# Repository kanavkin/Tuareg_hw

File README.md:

# Tuareg_hw
Tuareg board and schematics

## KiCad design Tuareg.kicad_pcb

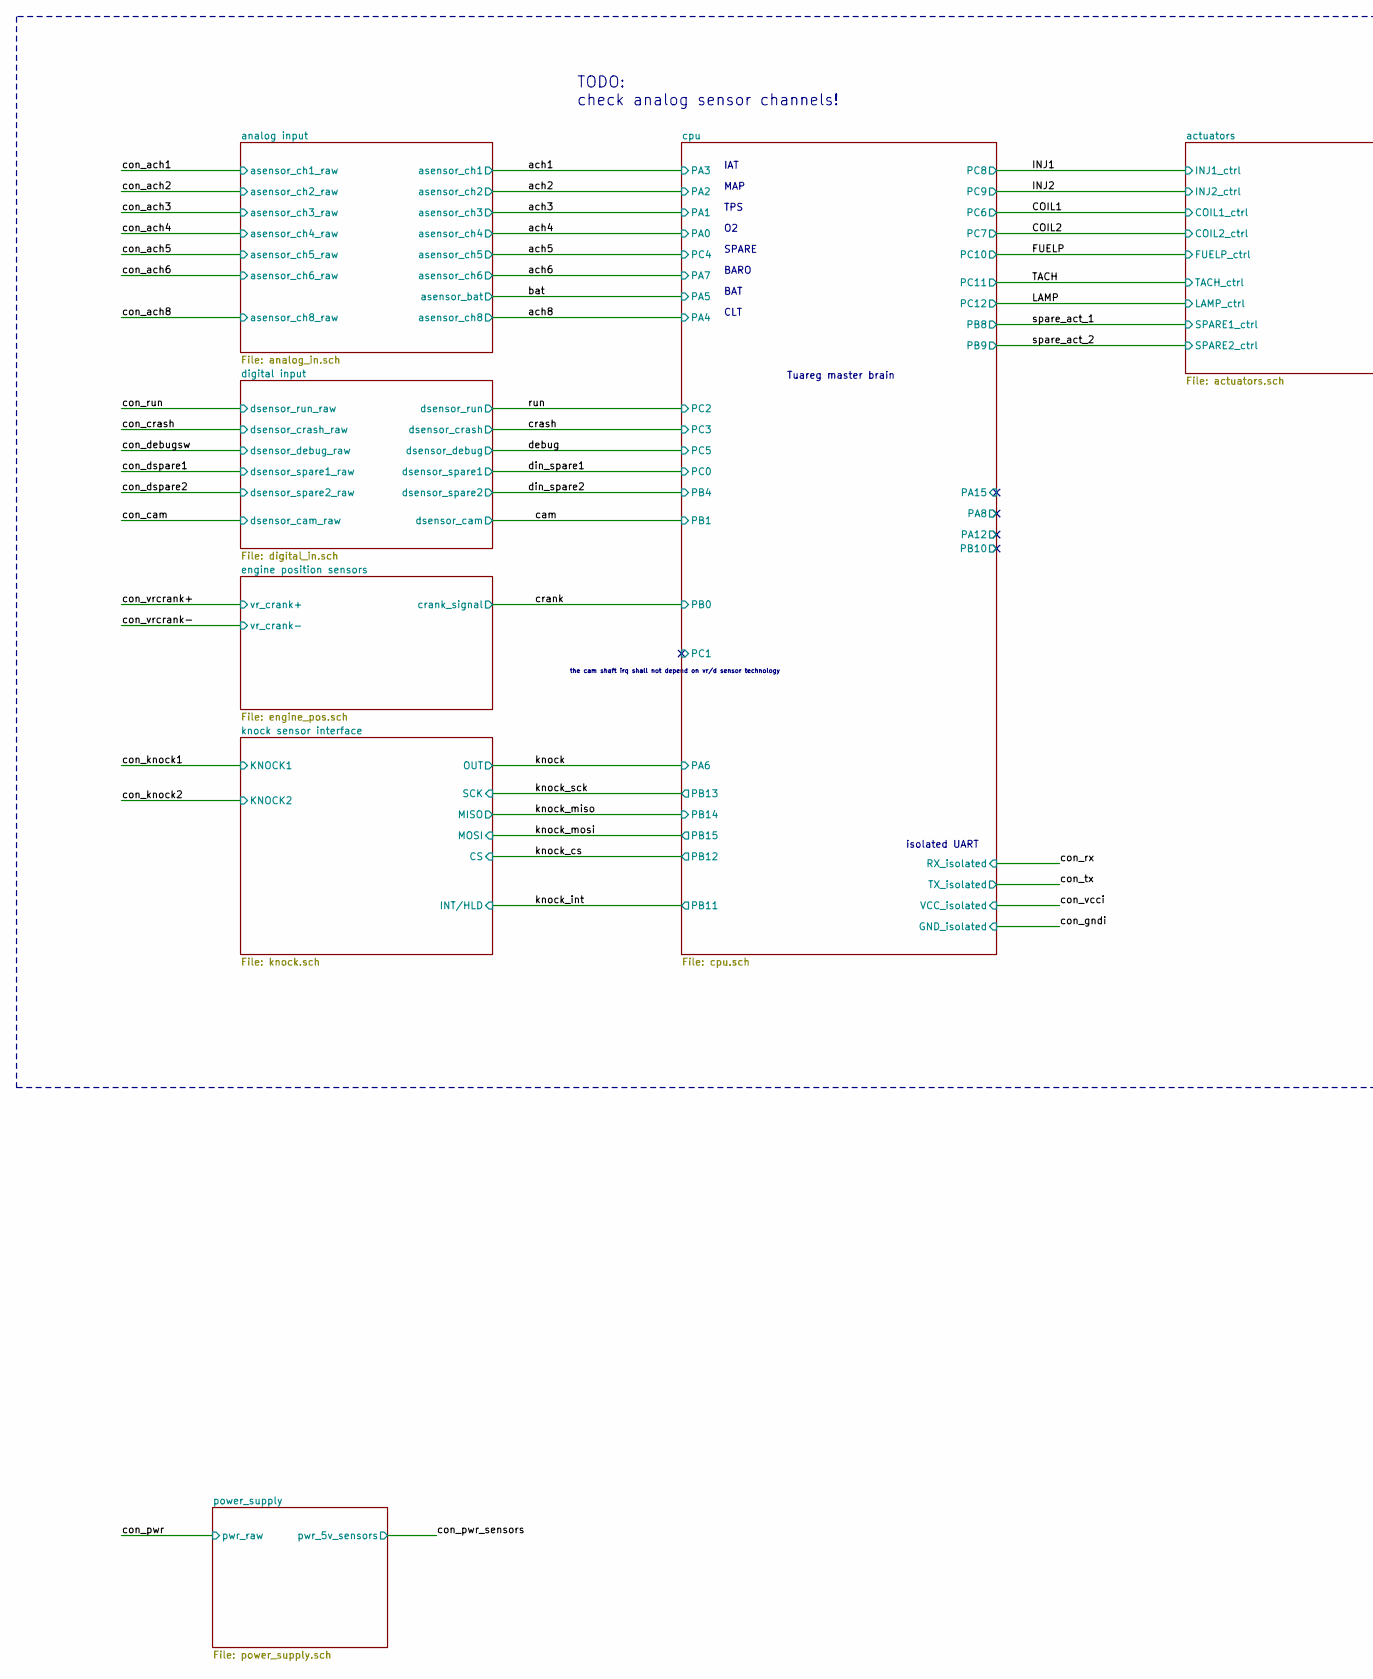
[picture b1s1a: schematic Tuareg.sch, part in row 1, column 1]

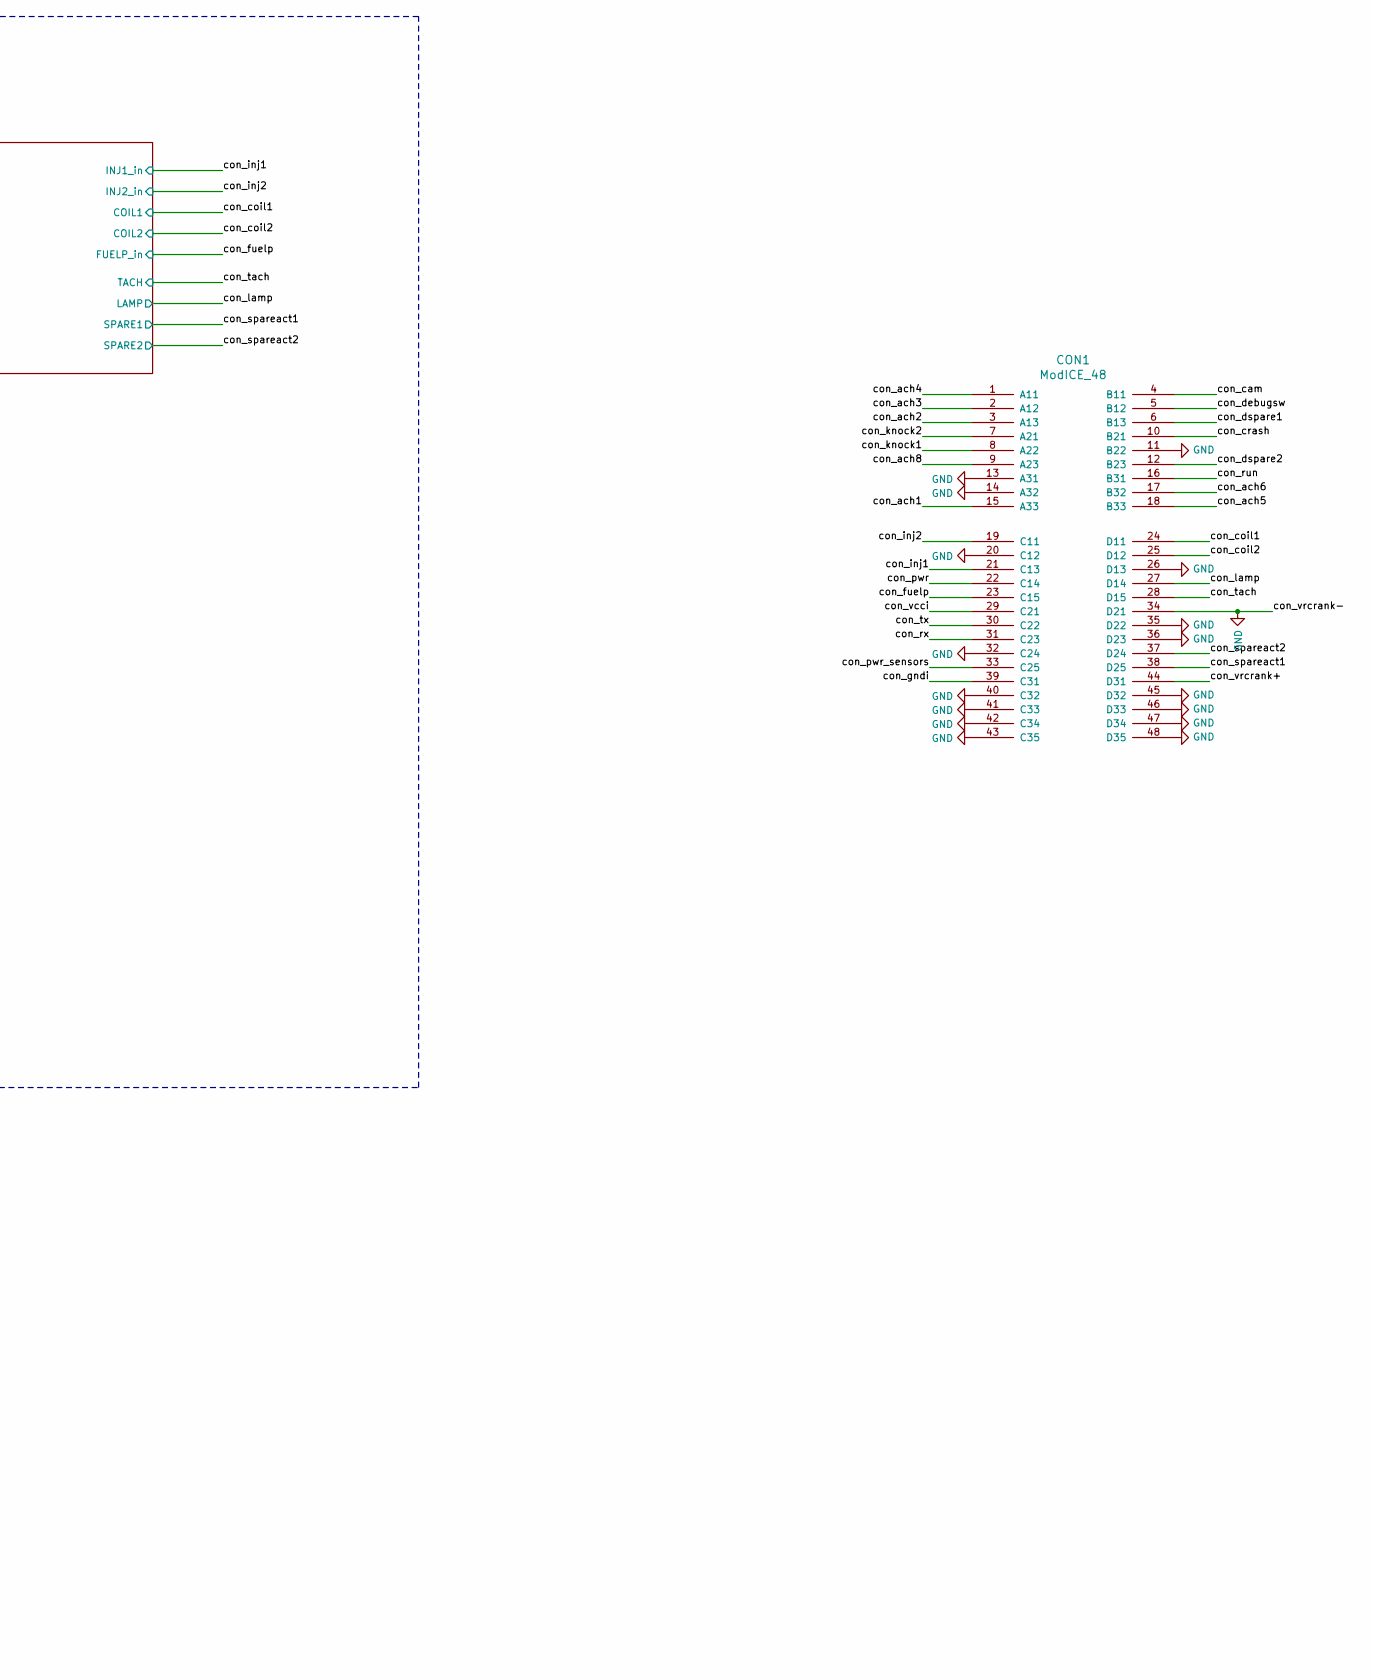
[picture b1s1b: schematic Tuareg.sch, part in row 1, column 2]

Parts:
CON1: ModICE_48; modICE_48

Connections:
/con_ach1: CON1.15 (A33); also elsewhere on the board
/con_ach2: CON1.3 (A13); also elsewhere on the board
/con_ach3: CON1.2 (A12); also elsewhere on the board
/con_ach4: CON1.1 (A11); also elsewhere on the board
/con_ach5: CON1.18 (B33); also elsewhere on the board
/con_ach6: CON1.17 (B32); also elsewhere on the board
/con_ach8: CON1.9 (A23); also elsewhere on the board
/con_cam: CON1.4 (B11); also elsewhere on the board
/con_coil1: CON1.24 (D11); also elsewhere on the board
/con_coil2: CON1.25 (D12); also elsewhere on the board
/con_crash: CON1.10 (B21); also elsewhere on the board
/con_debugsw: CON1.5 (B12); also elsewhere on the board
/con_dspare1: CON1.6 (B13); also elsewhere on the board
/con_dspare2: CON1.12 (B23); also elsewhere on the board
/con_fuelp: CON1.23 (C15); also elsewhere on the board
/con_gndi: CON1.39 (C31); also elsewhere on the board
/con_inj1: CON1.21 (C13); also elsewhere on the board
/con_inj2: CON1.19 (C11); also elsewhere on the board
/con_knock1: CON1.8 (A22); also elsewhere on the board
/con_knock2: CON1.7 (A21); also elsewhere on the board
/con_lamp: CON1.27 (D14); also elsewhere on the board
/con_pwr: CON1.22 (C14); also elsewhere on the board
/con_pwr_sensors: CON1.33 (C25); also elsewhere on the board
/con_run: CON1.16 (B31); also elsewhere on the board
/con_rx: CON1.31 (C23); also elsewhere on the board
/con_spareact1: CON1.38 (D25); also elsewhere on the board
/con_spareact2: CON1.37 (D24); also elsewhere on the board
/con_tach: CON1.28 (D15); also elsewhere on the board
/con_tx: CON1.30 (C22); also elsewhere on the board
/con_vcci: CON1.29 (C21); also elsewhere on the board
/con_vrcrank+: CON1.44 (D31); also elsewhere on the board
GND: CON1.11 (B22), CON1.13 (A31), CON1.14 (A32), CON1.20 (C12), CON1.26 (D13), CON1.32 (C24), CON1.34 (D21), CON1.35 (D22), CON1.36 (D23), CON1.40 (C32), CON1.41 (C33), CON1.42 (C34), CON1.43 (C35), CON1.45 (D32), CON1.46 (D33), CON1.47 (D34), CON1.48 (D35); also elsewhere on the board

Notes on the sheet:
Tuareg master brain
isolated UART
the cam shaft irq shall not depend on vr/d sensor technology
TPS
MAP
IAT
CLT
BAT
BARO
SPARE
TODO: check analog sensor channels!

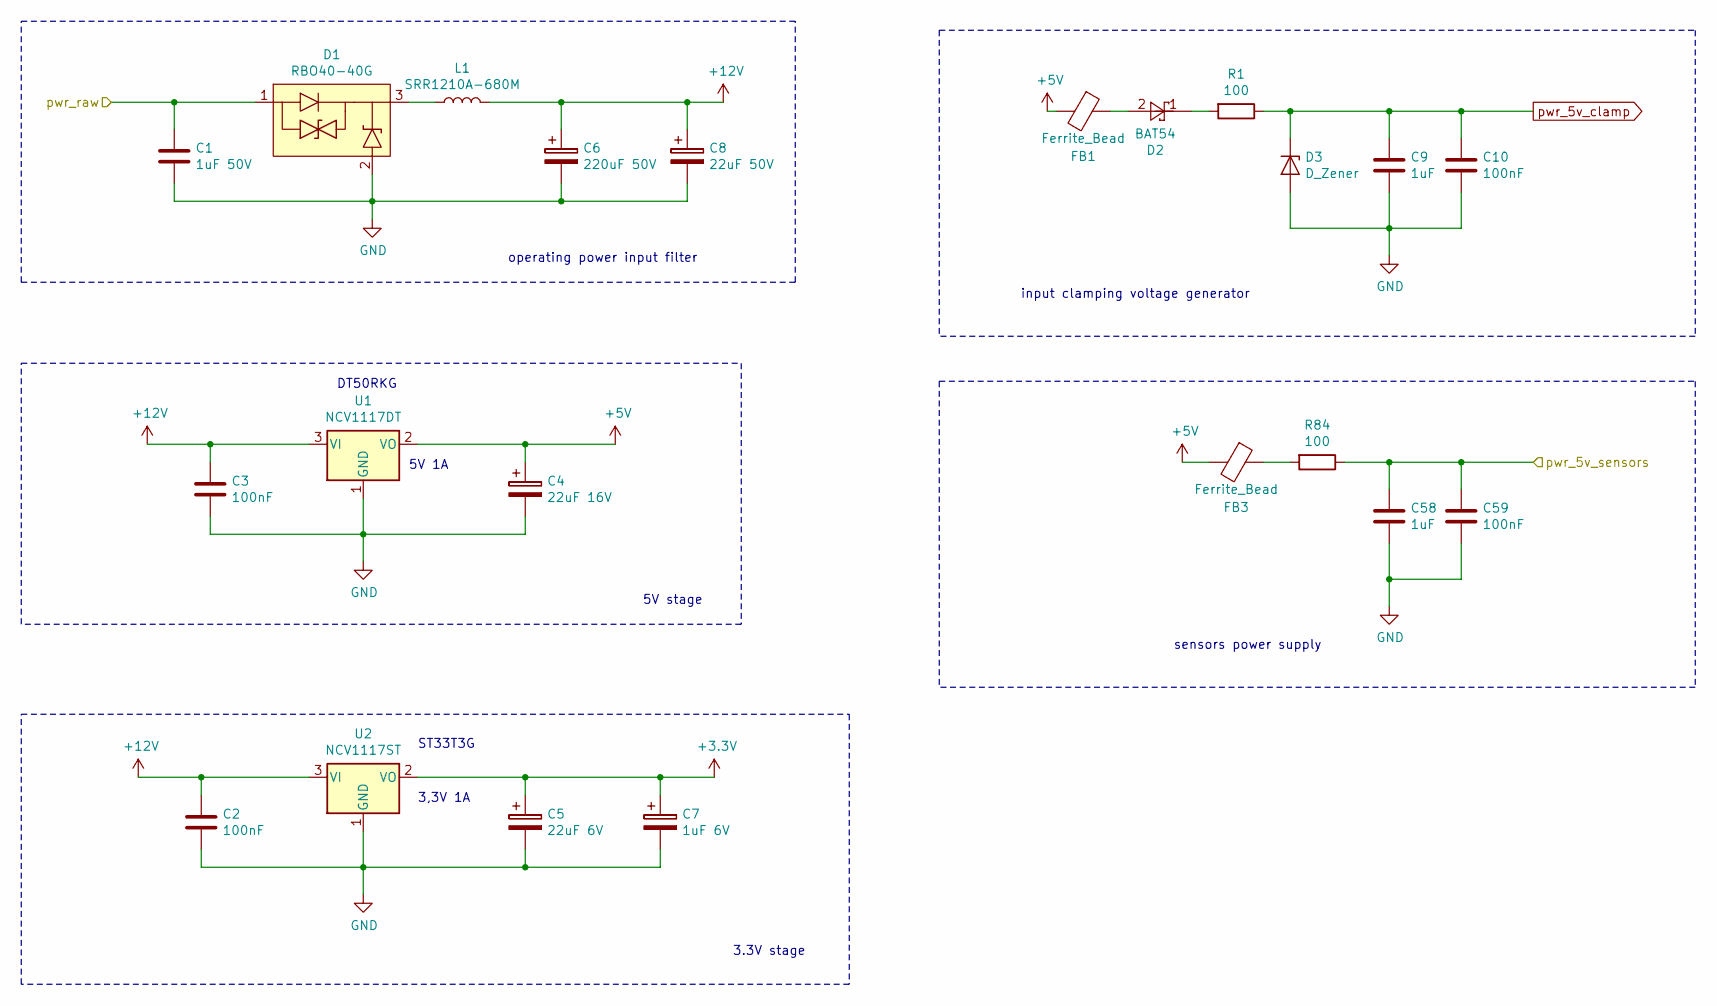
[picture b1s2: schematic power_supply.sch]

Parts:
C1: 1uF 50V; C_0805_2012Metric
C2, C3, C10, C59: 100nF; C_0805_2012Metric
C4: 22uF 16V; CP_Elec_5x5.8
C5: 22uF 6V; CP_Elec_4x5.8
C6: 220uF 50V; CP_Elec_6.3x7.7
C7: 1uF 6V; C_0805_2012Metric
C8: 22uF 50V; CP_Elec_6.3x7.7
C9, C58: 1uF; C_0805_2012Metric
D1: RBO40-40G
D2: BAT54; D_SOT-23_ANK
D3: D_Zener; D_MiniMELF
FB1, FB3: Ferrite_Bead; L_0805_2012Metric
L1: SRR1210A-680M; SRR1210A
R1, R84: 100; R_1210_3225Metric
U1: NCV1117DT
U2: NCV1117ST

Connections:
+3V3: C5.1, C7.1, U2.2 (VO); also elsewhere on the board
+5V: C4.1, FB1.2, FB3.2, U1.2 (VO); also elsewhere on the board
+12V: C2.1, C3.1, C6.1, C8.1, L1.2, U1.3 (VI), U2.3 (VI); also elsewhere on the board
/con_pwr: C1.1, D1.1 (IN); also elsewhere on the board
/con_pwr_sensors: C58.1, C59.1, R84.1; also elsewhere on the board
GND: C1.2, C2.2, C3.2, C4.2, C5.2, C6.2, C7.2, C8.2, C9.2, C10.2, C58.2, C59.2, D1.2 (GND), D3.2 (A), U1.1 (GND), U2.1 (GND); also elsewhere on the board
unnamed: D1.3 (OUT), L1.1
unnamed: D2.1, R1.2
unnamed: D2.2, FB1.1
unnamed: FB3.1, R84.2
pwr_5v_clamp: C9.1, C10.1, D3.1 (K), R1.1; also elsewhere on the board

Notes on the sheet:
operating power input filter
5V stage
3.3V stage
input clamping voltage generator
DT50RKG
5V 1A
ST33T3G
3,3V 1A
sensors power supply

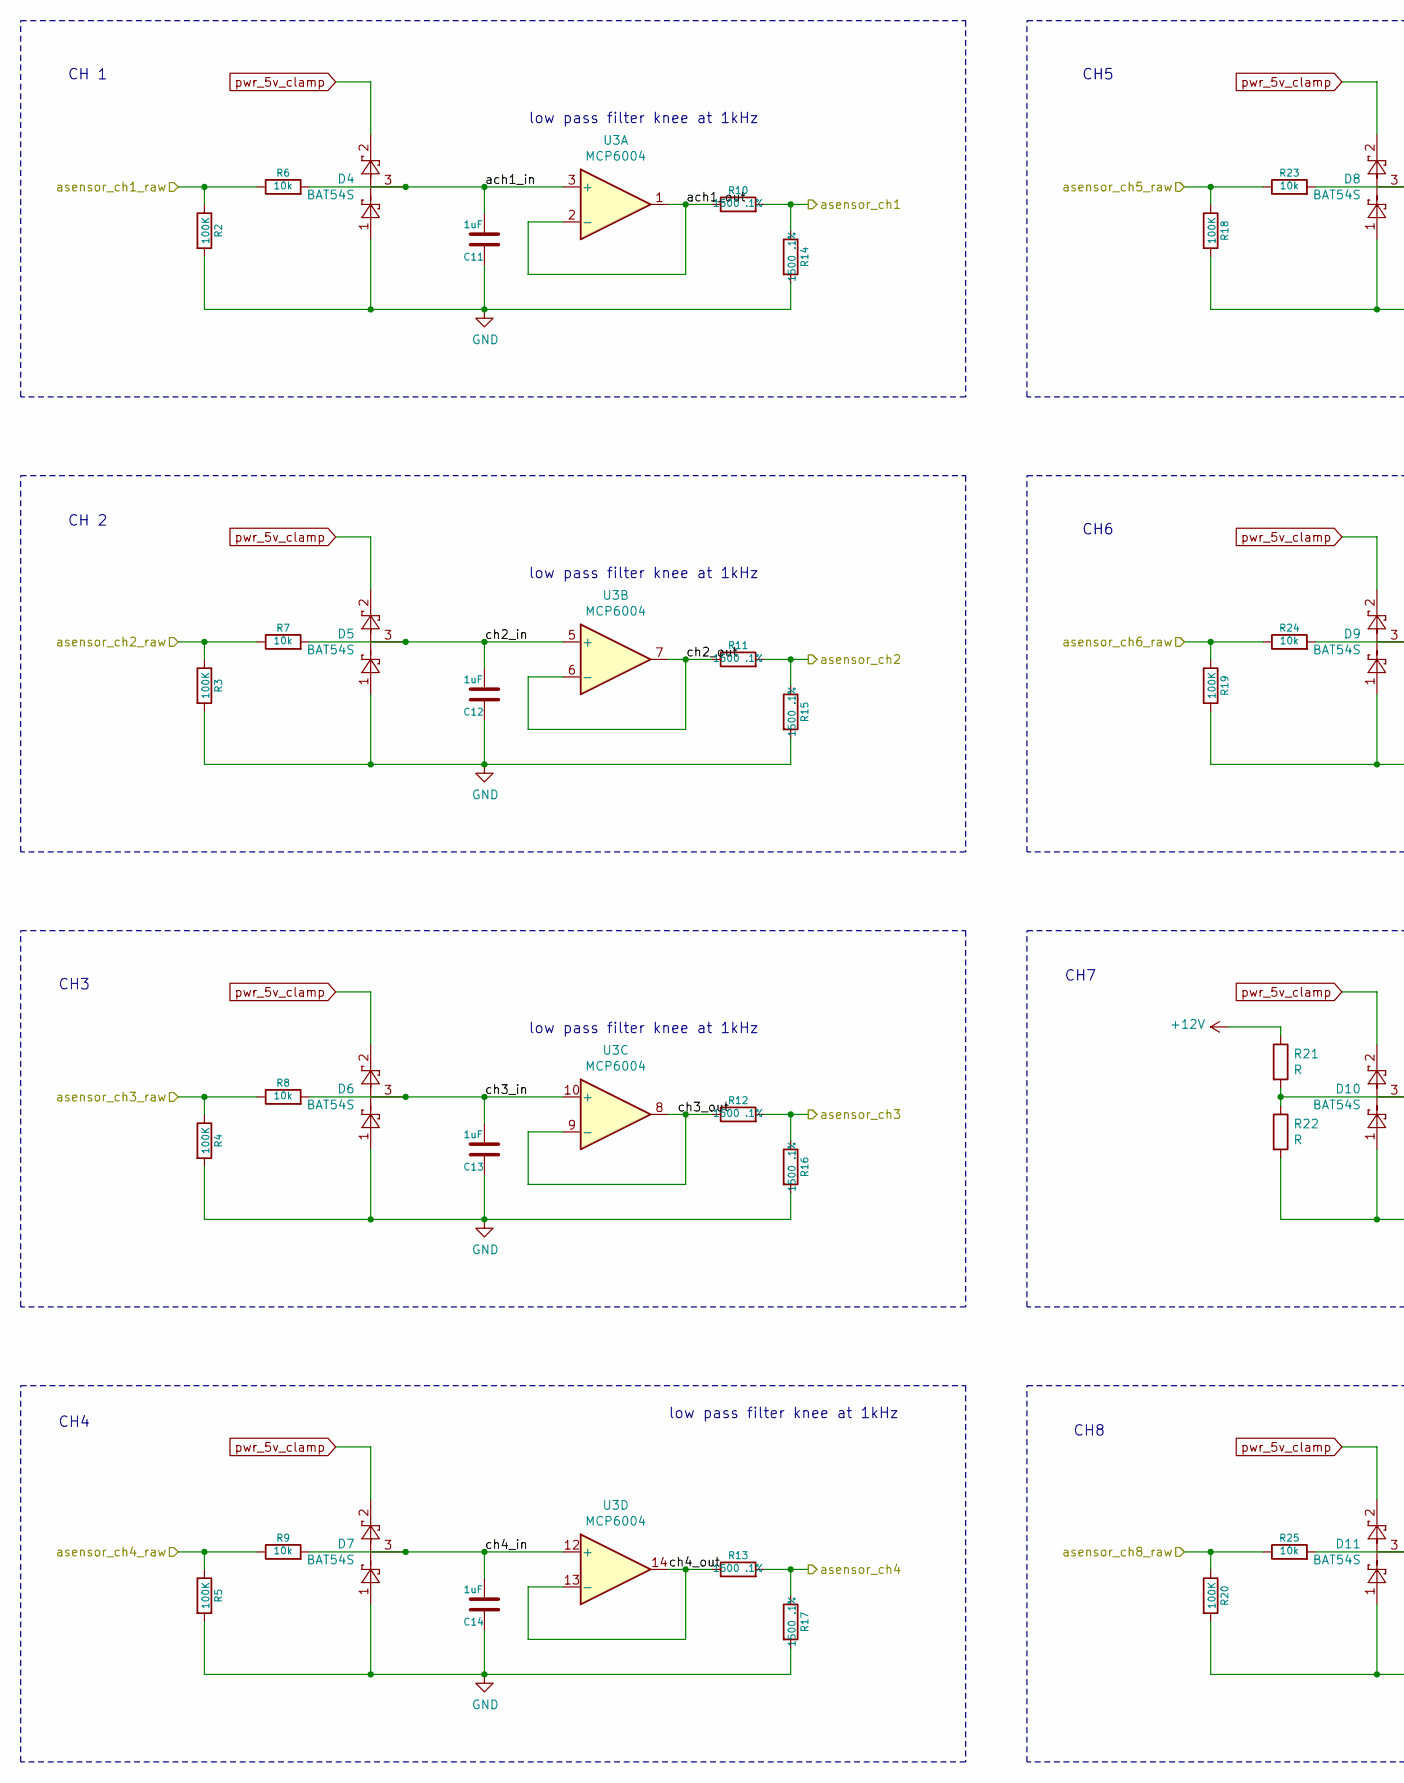
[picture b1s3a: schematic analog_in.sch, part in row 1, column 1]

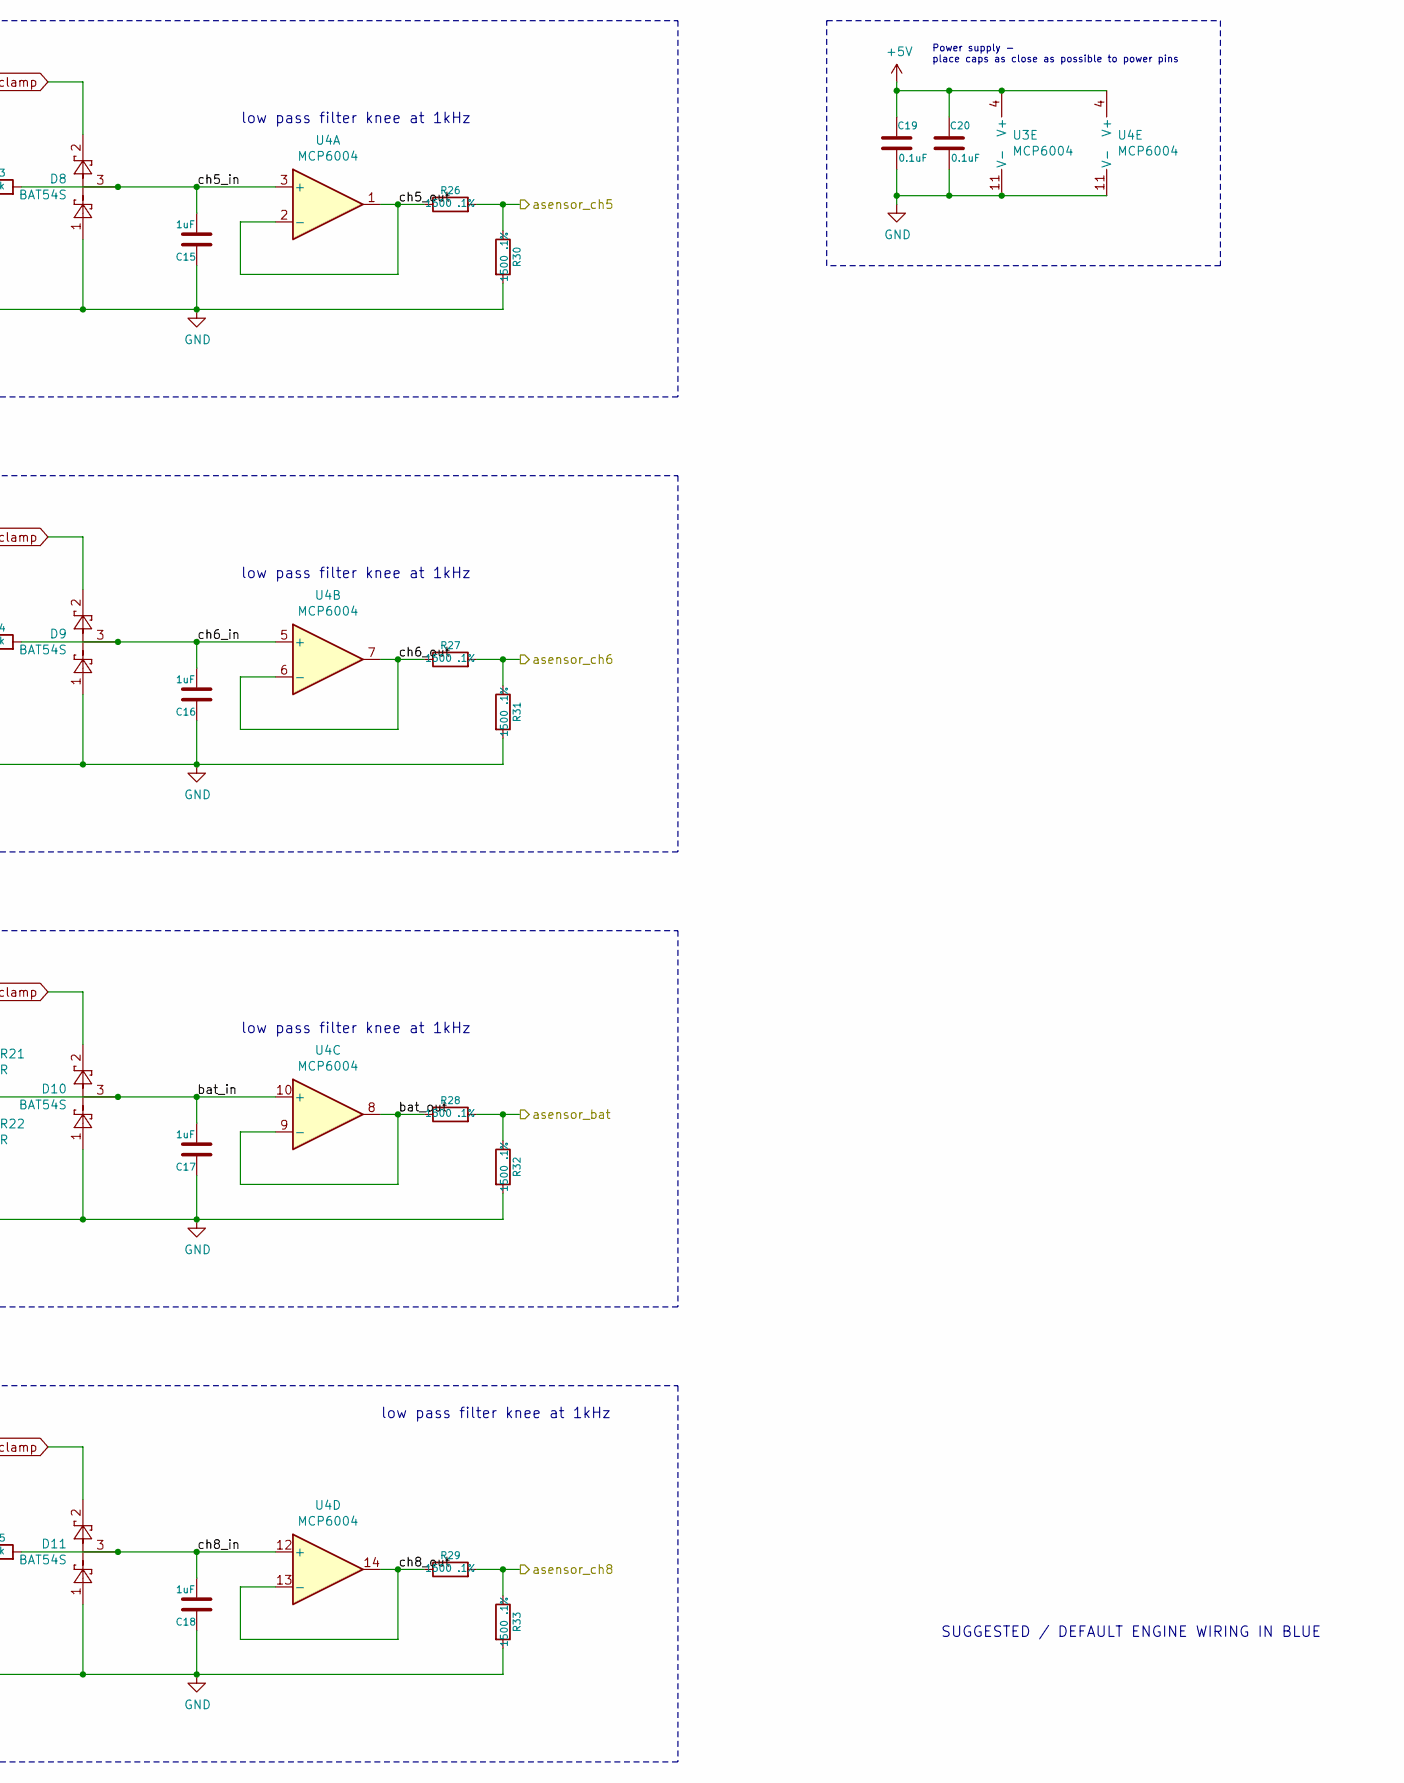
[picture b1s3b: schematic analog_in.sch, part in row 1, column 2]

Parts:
C11, C12, C13, C14, C15, C16, C17, C18: 1uF; C_0805_2012Metric
C19, C20: 0.1uF; C_0805_2012Metric
D4, D5, D6, D7, D8, D9, D10, D11: BAT54S; SOT-23
R2, R3, R4, R5, R18, R19, R20: 100K; R_0805_2012Metric
R6, R7, R8, R9, R23, R24, R25: 10k; R_0805_2012Metric
R10, R11, R12, R13, R14, R15, R16, R17, R26, R27, R28, R29, R30, R31, R32, R33: 1500 .1%; R_0805_2012Metric
R21, R22: R; R_1206_3216Metric
U3, U4: MCP6004

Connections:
+5V: C19.1, C20.1, U3.4 (V+), U4.4 (V+); also elsewhere on the board
+12V: R21.1; also elsewhere on the board
/ach1: R10.2, R14.1; also elsewhere on the board
/ach2: R11.2, R15.1; also elsewhere on the board
/ach3: R12.2, R16.1; also elsewhere on the board
/ach4: R13.2, R17.1; also elsewhere on the board
/ach5: R26.2, R30.1; also elsewhere on the board
/ach6: R27.2, R31.1; also elsewhere on the board
/ach8: R29.2, R33.1; also elsewhere on the board
/analog input/ach1_in: C11.2, D4.3, R6.2, U3.3 (+)
/analog input/ach1_out: R10.1, U3.1, U3.2 (-)
/analog input/bat_in: C17.2, D10.3, R21.2, R22.1, U4.10 (+)
/analog input/bat_out: R28.1, U4.8, U4.9 (-)
/analog input/ch2_in: C12.2, D5.3, R7.2, U3.5 (+)
/analog input/ch2_out: R11.1, U3.6 (-), U3.7
/analog input/ch3_in: C13.2, D6.3, R8.2, U3.10 (+)
/analog input/ch3_out: R12.1, U3.8, U3.9 (-)
/analog input/ch4_in: C14.2, D7.3, R9.2, U3.12 (+)
/analog input/ch4_out: R13.1, U3.13 (-), U3.14
/analog input/ch5_in: C15.2, D8.3, R23.2, U4.3 (+)
/analog input/ch5_out: R26.1, U4.1, U4.2 (-)
/analog input/ch6_in: C16.2, D9.3, R24.2, U4.5 (+)
/analog input/ch6_out: R27.1, U4.6 (-), U4.7
/analog input/ch8_in: C18.2, D11.3, R25.2, U4.12 (+)
/analog input/ch8_out: R29.1, U4.13 (-), U4.14
/bat: R28.2, R32.1; also elsewhere on the board
/con_ach1: R2.1, R6.1; also elsewhere on the board
/con_ach2: R3.1, R7.1; also elsewhere on the board
/con_ach3: R4.1, R8.1; also elsewhere on the board
/con_ach4: R5.1, R9.1; also elsewhere on the board
/con_ach5: R18.1, R23.1; also elsewhere on the board
/con_ach6: R19.1, R24.1; also elsewhere on the board
/con_ach8: R20.1, R25.1; also elsewhere on the board
GND: C11.1, C12.1, C13.1, C14.1, C15.1, C16.1, C17.1, C18.1, C19.2, C20.2, D4.1, D5.1, D6.1, D7.1, D8.1, D9.1, D10.1, D11.1, R2.2, R3.2, R4.2, R5.2, R14.2, R15.2, R16.2, R17.2, R18.2, R19.2, R20.2, R22.2, R30.2, R31.2, R32.2, R33.2, U3.11 (V-), U4.11 (V-); also elsewhere on the board
pwr_5v_clamp: D4.2, D5.2, D6.2, D7.2, D8.2, D9.2, D10.2, D11.2; also elsewhere on the board

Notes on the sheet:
SUGGESTED / DEFAULT ENGINE WIRING IN BLUE
CH 1
low pass filter knee at 1kHz
CH5
CH6
CH3
CH4
CH 2
CH7
CH8
Power supply - place caps as close as possible to power pins

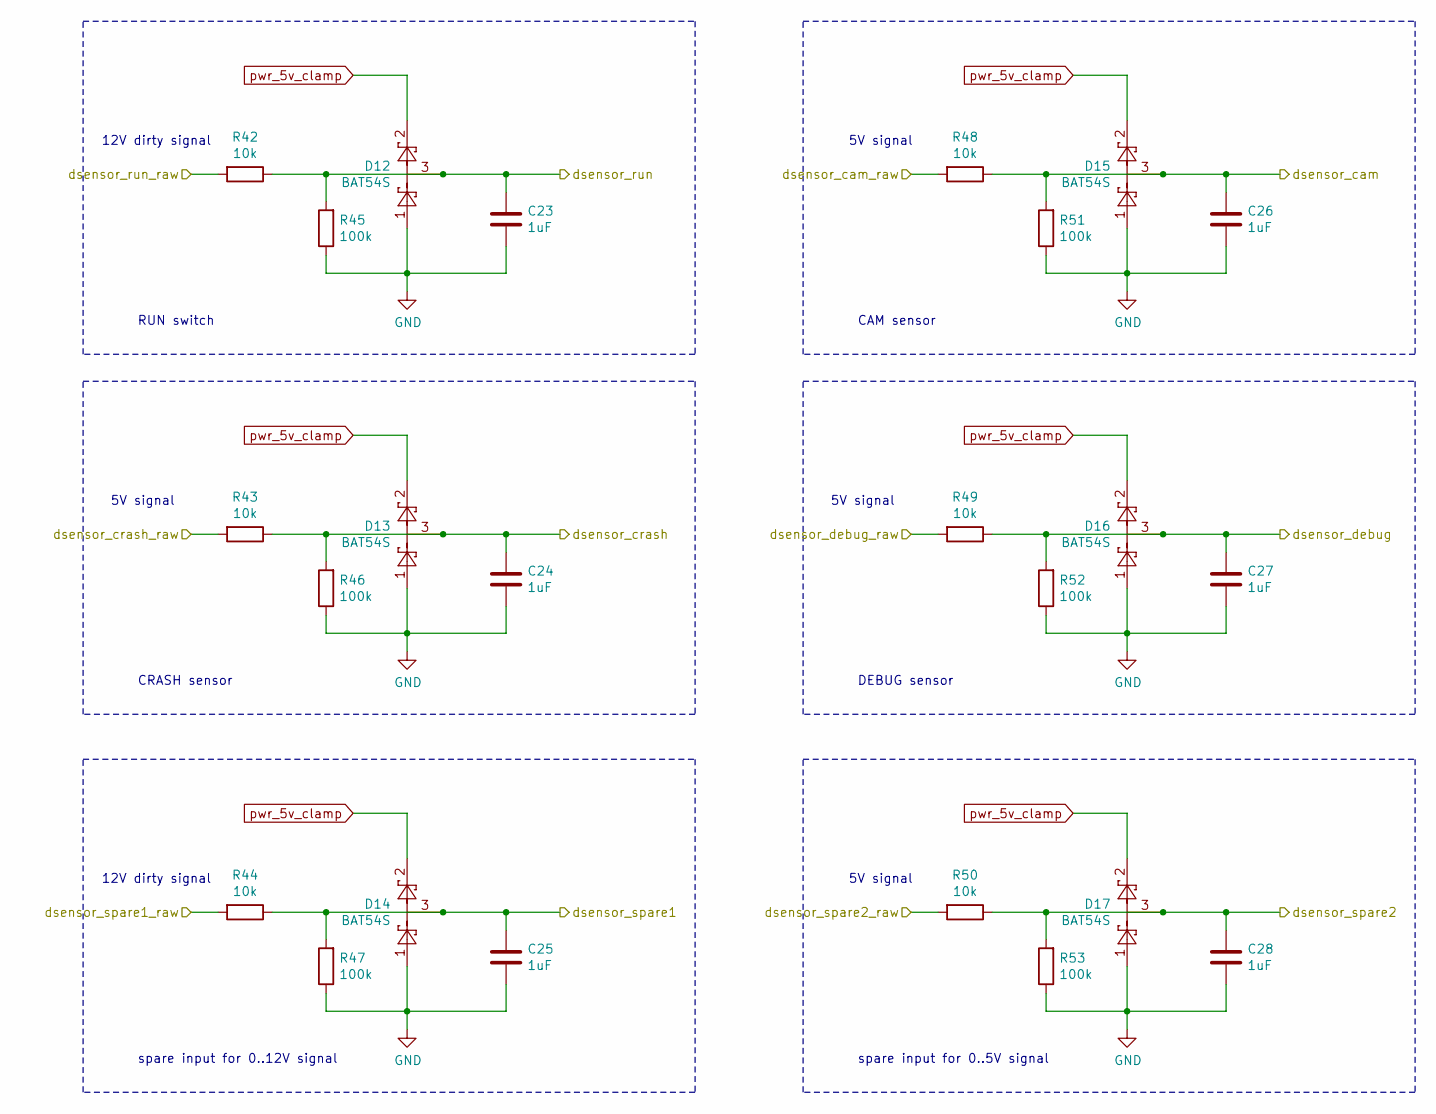
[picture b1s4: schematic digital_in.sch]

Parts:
C23, C24, C25, C26, C27, C28: 1uF; C_0805_2012Metric
D12, D13, D14, D15, D16, D17: BAT54S; SOT-23
R42, R43, R44, R48, R49, R50: 10k; R_0805_2012Metric
R45, R46, R47, R51, R52, R53: 100k; R_0805_2012Metric

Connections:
/cam: C26.1, D15.3, R48.1, R51.2; also elsewhere on the board
/con_cam: R48.2; also elsewhere on the board
/con_crash: R43.2; also elsewhere on the board
/con_debugsw: R49.2; also elsewhere on the board
/con_dspare1: R44.2; also elsewhere on the board
/con_dspare2: R50.2; also elsewhere on the board
/con_run: R42.2; also elsewhere on the board
/crash: C24.1, D13.3, R43.1, R46.2; also elsewhere on the board
/debug: C27.1, D16.3, R49.1, R52.2; also elsewhere on the board
/din_spare1: C25.1, D14.3, R44.1, R47.2; also elsewhere on the board
/din_spare2: C28.1, D17.3, R50.1, R53.2; also elsewhere on the board
/run: C23.1, D12.3, R42.1, R45.2; also elsewhere on the board
GND: C23.2, C24.2, C25.2, C26.2, C27.2, C28.2, D12.1, D13.1, D14.1, D15.1, D16.1, D17.1, R45.1, R46.1, R47.1, R51.1, R52.1, R53.1; also elsewhere on the board
pwr_5v_clamp: D12.2, D13.2, D14.2, D15.2, D16.2, D17.2; also elsewhere on the board

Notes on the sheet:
RUN switch
CRASH sensor
spare input for 0..12V signal
CAM sensor
12V dirty signal
5V signal
DEBUG sensor
spare input for 0..5V signal

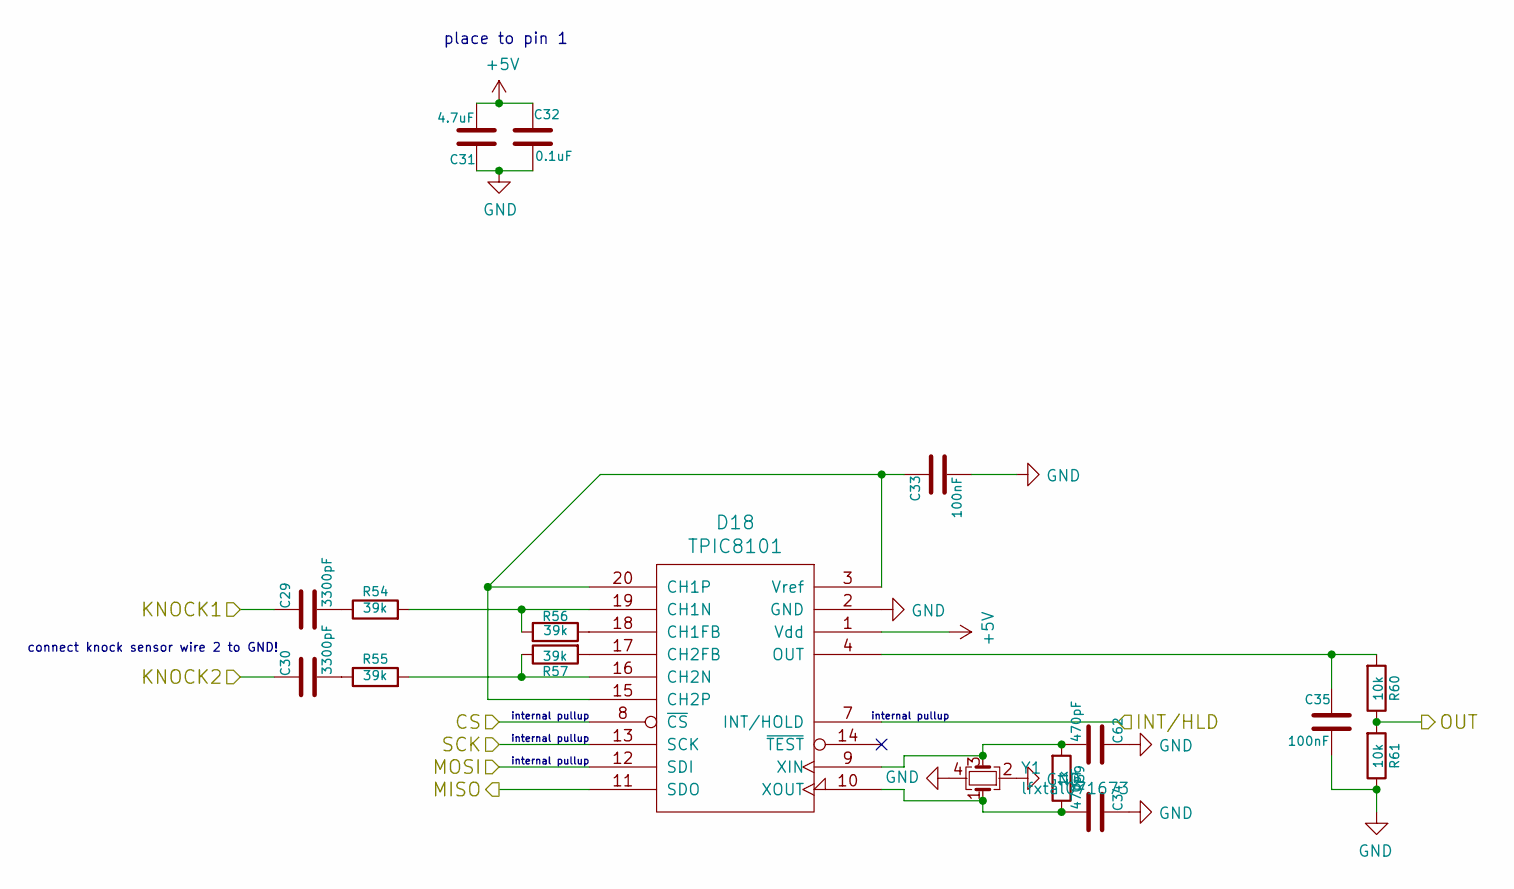
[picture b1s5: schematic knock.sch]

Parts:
C29, C30: 3300pF; C_0805_2012Metric
C31: 4.7uF; C_0805_2012Metric
C32: 0.1uF; C_0805_2012Metric
C33, C35: 100nF; C_0805_2012Metric
C34, C62: 470pF; C_0805_2012Metric
D18: TPIC8101
R54, R55, R56, R57: 39k; R_0805_2012Metric
R59: 1k; R_0805_2012Metric
R60, R61: 10k; R_0805_2012Metric
Y1: lfxtal071673

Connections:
+5V: C31.2, C32.1, D18.1 (Vdd); also elsewhere on the board
/con_knock1: C29.1; also elsewhere on the board
/con_knock2: C30.1; also elsewhere on the board
/knock: R60.1, R61.2; also elsewhere on the board
/knock_cs: D18.8 (~CS~); also elsewhere on the board
/knock_int: D18.7 (INT/HOLD); also elsewhere on the board
/knock_miso: D18.11 (SDO); also elsewhere on the board
/knock_mosi: D18.12 (SDI); also elsewhere on the board
/knock_sck: D18.13 (SCK); also elsewhere on the board
GND: C31.1, C32.2, C33.2, C34.1, C35.2, C62.1, D18.2 (GND), R61.1, Y1.2, Y1.4; also elsewhere on the board
unnamed: C29.2, R54.1
unnamed: C30.2, R55.1
unnamed: C33.1, D18.3 (Vref), D18.15 (CH2P), D18.20 (CH1P)
unnamed: C34.2, D18.10 (XOUT), R59.1, Y1.1
unnamed: C35.1, D18.4 (OUT), R60.2
unnamed: C62.2, D18.9 (XIN), R59.2, Y1.3
unnamed: D18.16 (CH2N), R55.2, R57.1
unnamed: D18.17 (CH2FB), R57.2
unnamed: D18.18 (CH1FB), R56.1
unnamed: D18.19 (CH1N), R54.2, R56.2

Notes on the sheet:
internal pullup
place to pin 1
connect knock sensor wire 2 to GND!
